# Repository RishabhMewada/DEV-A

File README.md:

# DEV-A

A Devboard made with the RP2040 microcontroller , designed specifically for projects integration

## What is DEV-A?
Dev-A is an devboard based on the RP2040 microcontroller , made for projects integration , while it is based on the rassberry pi pico

<p align="center">

## Features
- The RP2040 microcontrol capable of integrations into any mini hobby projects
- Type-c port capable of flashing into the emmmc fast and quick and efficent power supply
- Pin headers , can connect into any breadboard and jupper pins , making it easy for integration

 <p align="center">

## Parts

- RP2040 (Microcontroller)
- eMMC (Flash memory)
- charging ic ( voltage controller)
- Type-c female connector
- pin headers (2x20 pin , 1x3 pin)
- crystal 12Mhz 
- capacitors , resistors 
- push button 

 <p align="center">

## Files attached
- Project files (SCH , PCB , CIRCUIT)
- CAD ( autodesk files , STEP file)
- Firmware (Aurdino IDE)
- Images

  <p align="center">

## License 

MIT Open-source License

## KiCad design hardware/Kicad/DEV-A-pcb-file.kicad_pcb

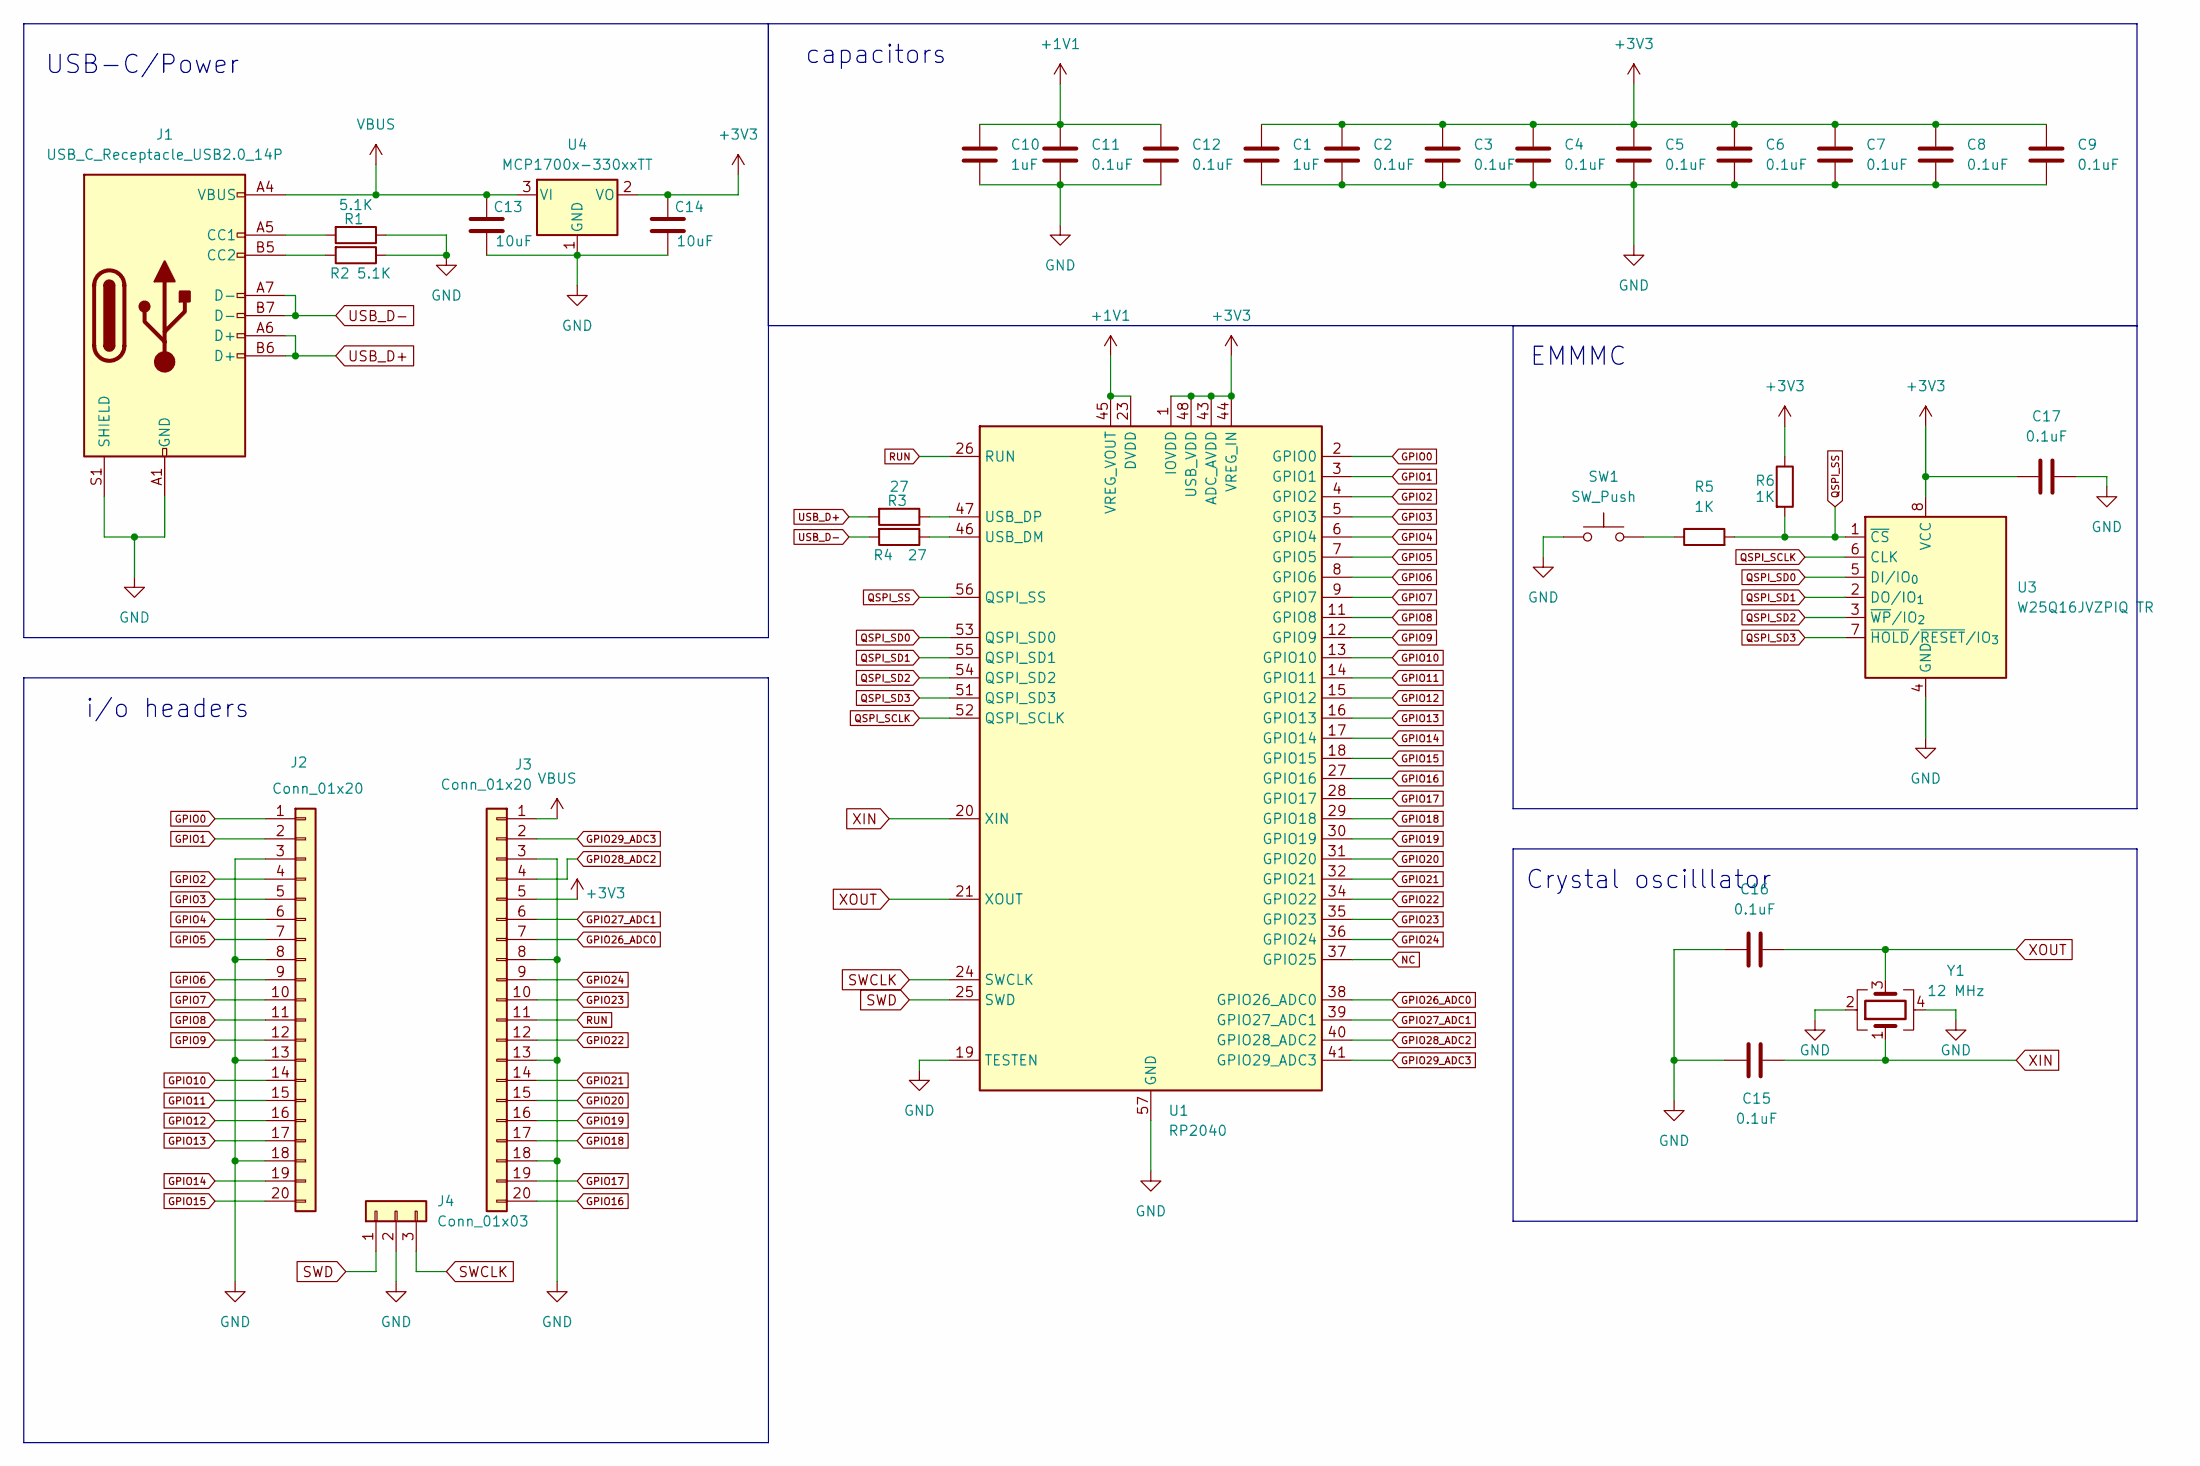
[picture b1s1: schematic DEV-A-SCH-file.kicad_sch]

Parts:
C1, C10: 1uF; C_0402_1005Metric
C2, C3, C4, C5, C6, C7, C8, C9, C11, C12, C15, C16, C17: 0.1uF; C_0402_1005Metric
C13, C14: 10uF; C_0603_1608Metric
J1: USB_C_Receptacle_USB2.0_14P; USB_C_Receptacle_HRO_TYPE-C-31-M-12
J2, J3: Conn_01x20; PinHeader_1x20_P2.54mm_Vertical
J4: Conn_01x03; PinHeader_1x03_P2.54mm_Vertical
R1, R2: 5.1K; R_0402_1005Metric
R3, R4: 27; R_0402_1005Metric
R5, R6: 1K; R_0402_1005Metric
SW1: SW_Push; SW_Push_SPST_NO_Alps_SKRK
U1: RP2040; QFN-56-1EP_7x7mm_P0.4mm_EP3.2x3.2mm
U3: W25Q16JVZPIQ TR; Winbond_USON-8-1EP_3x2mm_P0.5mm_EP0.2x1.6mm
U4: MCP1700x-330xxTT; SOT-23
Y1: 12 MHz; Crystal_SMD_3225-4Pin_3.2x2.5mm

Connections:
GPIO0: J2.1, U1.2 (GPIO0)
GPIO1: J2.2, U1.3 (GPIO1)
GPIO2: J2.4, U1.4 (GPIO2)
GPIO3: J2.5, U1.5 (GPIO3)
GPIO4: J2.6, U1.6 (GPIO4)
GPIO5: J2.7, U1.7 (GPIO5)
GPIO6: J2.9, U1.8 (GPIO6)
GPIO7: J2.10, U1.9 (GPIO7)
GPIO8: J2.11, U1.11 (GPIO8)
GPIO9: J2.12, U1.12 (GPIO9)
GPIO10: J2.14, U1.13 (GPIO10)
GPIO11: J2.15, U1.14 (GPIO11)
GPIO12: J2.16, U1.15 (GPIO12)
GPIO13: J2.17, U1.16 (GPIO13)
GPIO14: J2.19, U1.17 (GPIO14)
GPIO15: J2.20, U1.18 (GPIO15)
GPIO16: J3.20, U1.27 (GPIO16)
GPIO17: J3.19, U1.28 (GPIO17)
GPIO18: J3.17, U1.29 (GPIO18)
GPIO19: J3.16, U1.30 (GPIO19)
GPIO20: J3.15, U1.31 (GPIO20)
GPIO21: J3.14, U1.32 (GPIO21)
GPIO22: J3.12, U1.34 (GPIO22)
GPIO23: J3.10, U1.35 (GPIO23)
GPIO24: J3.9, U1.36 (GPIO24)
GPIO26_ADC0: J3.7, U1.38 (GPIO26_ADC0)
GPIO27_ADC1: J3.6, U1.39 (GPIO27_ADC1)
GPIO28_ADC2: J3.4, U1.40 (GPIO28_ADC2)
GPIO29_ADC3: J3.2, U1.41 (GPIO29_ADC3)
NC: U1.37 (GPIO25)
QSPI_SCLK: U1.52 (QSPI_SCLK), U3.6 (CLK)
QSPI_SD0: U1.53 (QSPI_SD0), U3.5 (DI/IO_{0})
QSPI_SD1: U1.55 (QSPI_SD1), U3.2 (DO/IO_{1})
QSPI_SD2: U1.54 (QSPI_SD2), U3.3 (~WP/IO_{2})
QSPI_SD3: U1.51 (QSPI_SD3), U3.7 (~HOLD/~RESET/IO_{3})
QSPI_SS: R5.2, R6.2, U1.56 (QSPI_SS), U3.1 (~CS)
RUN: J3.11, U1.26 (RUN)
SWD: J4.1, U1.25 (SWD)
+1V1: C10.1, C11.1, C12.1, U1.23 (DVDD), U1.45 (VREG_VOUT), U1.50 (DVDD)
+3V3: C1.1, C2.1, C3.1, C4.1, C5.1, C6.1, C7.1, C8.1, C9.1, C14.1, C17.1, J3.5, R6.1, U1.1 (IOVDD), U1.10 (IOVDD), U1.22 (IOVDD), U1.33 (IOVDD), U1.42 (IOVDD), U1.43 (ADC_AVDD), U1.44 (VREG_IN), U1.48 (USB_VDD), U1.49 (IOVDD), U3.8 (VCC), U4.2 (VO)
GND: C1.2, C2.2, C3.2, C4.2, C5.2, C6.2, C7.2, C8.2, C9.2, C10.2, C11.2, C12.2, C13.2, C14.2, C15.2, C16.1, C17.2, J1.A1 (GND), J1.A12 (GND), J1.B1 (GND), J1.B12 (GND), J1.S1 (SHIELD), J2.3, J2.8, J2.13, J2.18, J3.3, J3.8, J3.13, J3.18, J4.2, R1.1, R2.1, SW1.1, U1.19 (TESTEN), U1.57 (GND), U3.4 (GND), U4.1 (GND), Y1.2, Y1.4
unnamed: J1.A5 (CC1), R1.2
unnamed: J1.B5 (CC2), R2.2
unnamed: R5.1, SW1.2
unnamed: R4.1, U1.46 (USB_DM)
unnamed: R3.1, U1.47 (USB_DP)
SWCLK: J4.3, U1.24 (SWCLK)
USB_D+: J1.A6 (D+), J1.B6 (D+), R3.2
USB_D-: J1.A7 (D-), J1.B7 (D-), R4.2
VBUS: C13.1, J1.A4 (VBUS), J1.A9 (VBUS), J1.B4 (VBUS), J1.B9 (VBUS), J3.1, U4.3 (VI)
XIN: C15.1, U1.20 (XIN), Y1.1
XOUT: C16.2, U1.21 (XOUT), Y1.3

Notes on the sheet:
i/o headers
Crystal oscilllator
EMMMC
USB-C/Power
capacitors

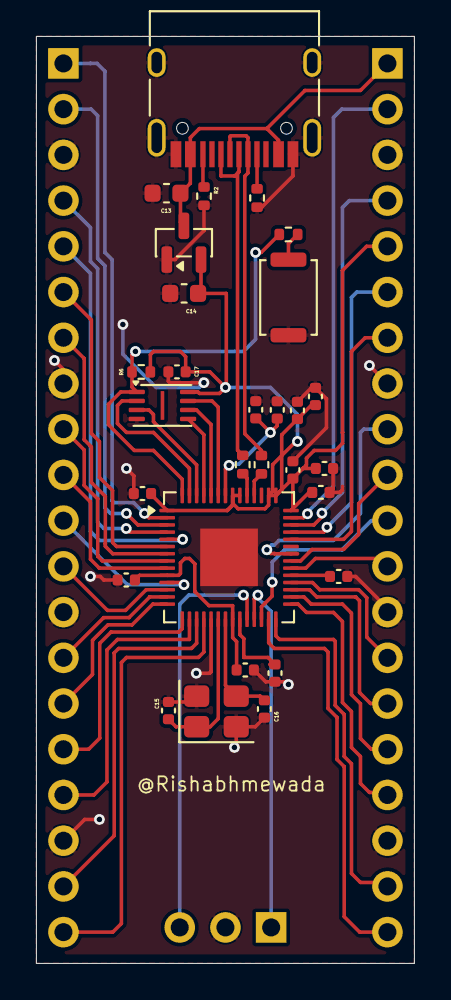
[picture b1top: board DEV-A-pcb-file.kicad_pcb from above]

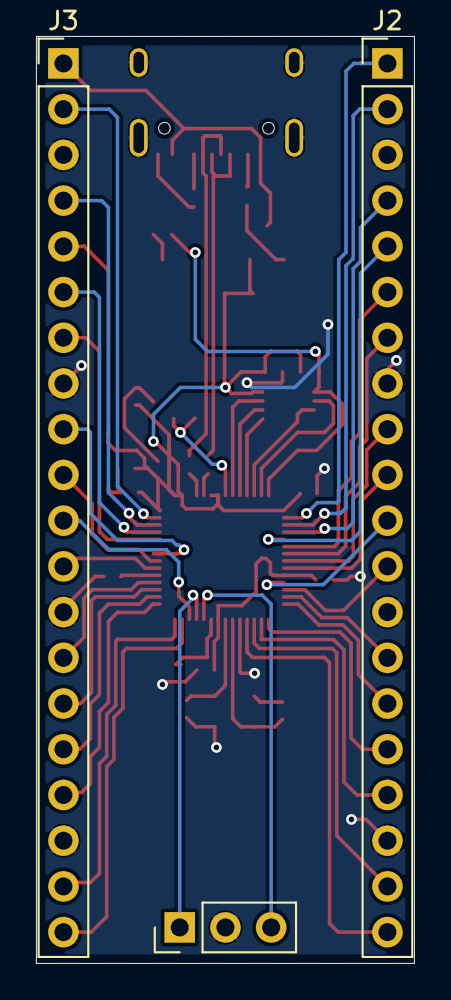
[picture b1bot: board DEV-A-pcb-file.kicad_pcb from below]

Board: 2 copper layers, 21.0 x 51.5 mm, 32 parts (3 on the bottom side), 51 nets.

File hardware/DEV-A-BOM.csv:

Name,Purpose,Quantity,Total Cost (USD),Link,Distributor
"Heat Insulation Silicone Working Mat 30*20cm","mat.",1,2.30,"https://robu.in/product/heat-insulation-silicone-working-mat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","Robu.in"
"SOLDERING KIT","its my first time soldering , i dont have any equipment , can i get it pleasee!",1,18.95,"https://robu.in/product/pro-range-soldering-iron-kit-with-sm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","Robu.in"
"PCB ","PCB BOARD",5,7.74,"https://cart.jlcpcb.com/shopcart/cart/","JLPCB"
"conn_01x20 pin header","pin header",2,0.41,"https://robu.in/product/a2541wv-20p-9t-cjt-1x20-pin-2-54mm-1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","Robu"
"RP2040","MICRO CONTROLLER",1,0.87,"https://robu.in/product/raspberry-pi-rp2040/","Robu.in"
"8Z-12.000MAAJ-T – 12MHz ±30ppm Crystal 18pF","12Mhz CRYSTAL",1,1.08,"https://robu.in/product/8z-12-000maaj-t-12mhz-%c2%b130ppm-cr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","Robu.in"
"MCP1700T-3302E/TT","CHARGING IC",1,0.42,"https://robu.in/product/mcp1700t-3302e-tt-microchip-technolo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","Robu.in"
"eMMC","spi flash",1,0.84,"https://robu.in/product/w25q16jvzpiq-winbond-electronics-16m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","Robu.in"
"Resistor R5,R6","RESISTOR (1K)",2,0.08,"https://robu.in/product/1k-resistor-smdr-0402-pack-of-50/","Robu.in"
"Resistor R3,R4","RESISTOR (27 ohm)",2,0.06,"https://robu.in/product/erj2rkf27r0x-panasonic-smd-chip-resi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","Robu.in"
"Resistor R1,R2","RESISTOR 5.1K",2,0.08,"https://robu.in/product/1k-resistor-smdr-0402-pack-of-50/","Robu.in"
"USB_type_c female connector","power",1,0.41,"https://robu.in/product/type-c-31-m-12-hroparts-5a-1-16p-fem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","Robu.in"
"capacitors , C13,C14","CAPACITORS (10uF)",10,0.09,"https://robu.in/product/0603x106m100nt-fh-10v-10uf-x5r%c2%b1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","Robu.in"
"Capacitors C1,C10","Capacitors (1uF)",10,0.37,"https://robu.in/product/1uf-1000nf-50v-capacitor-1206-smd-pa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","robu.in"
"Capacitor C2-C9 ,C11-C12 ,C15-C17","capacitor (0.1uF) extra capacitors in case i blow it up all",24,0.10,"https://robu.in/product/0-1uf-capacitor-smdc-0603/","Robu.in"
